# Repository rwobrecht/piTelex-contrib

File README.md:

# Willkommen zu meinem piTelex-contrib

Hier sammle ich Anpassungen und anderes, was ich rund um piTelex mal entwickelt habe, in der Hoffnung, dass der eine oder andere piTelex-Nutzer mit der einen oder anderen Sache etwas anfangen kann, und -nicht zu vergessen- damit ich die Sachen bei Bedarf auch selbst wiederfinde :-)

## piTelex-Hardware für TW39

- ### Kombi-Platine für Linienstrommaschinen mit und ohne Fernschaltgerät

  jumper-konfigurierbar für Betrieb mit/ohne FSG

  - [TW39-Platine](TW39/Kombiversion/TW39-mit-Powersave) für einen RaspBerry Pi mit Powersave-Funktion sowohl für die 230V-Versorgung als auch für die Linienstromversorgung.
  - [TW39-Stromversorgung](TW39/Kombiversion/Stromversorgung-für-TW39-mit-Powersave) dazu passend, mit Powersave-Unterstützung.

- ### als Fernschaltgerät-Ersatz für Linienstrommaschinen mit 24V-LED-Treiber

  * [TW39-Platine](TW39/Ohne-FSG/TW39-ohne-FSG-mit-Powersave) für einen RaspBerry Pi als vollwertiger FSG-Ersatz mit Powersave-Funktion sowohl für die 230V-Versorgung als auch für die Linienstromversorgung

  * [TW39-Stromversorgung](TW39/Ohne-FSG//Stromversorgung-für-TW39-ohne-FSG-mit-Powersave) mit reduzierter Linienspannung, dazu passend. 

  * [Aufbaubeispiel mit Steckernetzteil und Kleinspannung](TW39/Ohne-FSG/Aufbaubeispiel/)

- ### [Adapterplatinchen zum Anschluss eines Tastwahlblocks](TW39/TWB/)

- ###  für V.10
  * [V.10-Platine](V10/V.10-3-mit-Powersave) für die Anbindung von TeKaDe FS200/FS220 mit Powersave-Funktion

  * [V.10-Stromversorgung](V10/V.10-3-Stromversorgung-mit-Powersave) dazu passend, mit Powersave-Unterstützung für die 230V-Versorgung.

  * [Aufbaubeispiel](V10/Aufbaubeispiel/README.md)

**Fragen oder Anregungen gerne an `telex(at)freenet.de`.**

**Da bei meinem PCB Hersteller immer eine Mindestabnahme gilt, und ich selber die Platinen nicht alle "verbrauchen" kann, gebe ich vorhandenes Material gerne weiter. Bei Interesse einfach nachfragen!**

## Software: RPi-Image mit piTelex

- ### RPi-Image mit piTelex

  Zu den o.a. Hardware-Varianten  [passendes Software-Image](./soft/rpi-image/README.md) für RaspBerry Pi's. Es enthält ein fertig vorinstalliertes und lauffähiges piTelex.
  
- ### Device modul für LCD1602 Display

  Statt der LEDs (oder ergänzend) ein [zweizeiliges LCD](./soft/LCD1602/README.md)  **mit Rufnummernanzeige** einbinden

## HOWTOS und so...

Unter [HOWTO](HOWTO) ...passenderweise :-)

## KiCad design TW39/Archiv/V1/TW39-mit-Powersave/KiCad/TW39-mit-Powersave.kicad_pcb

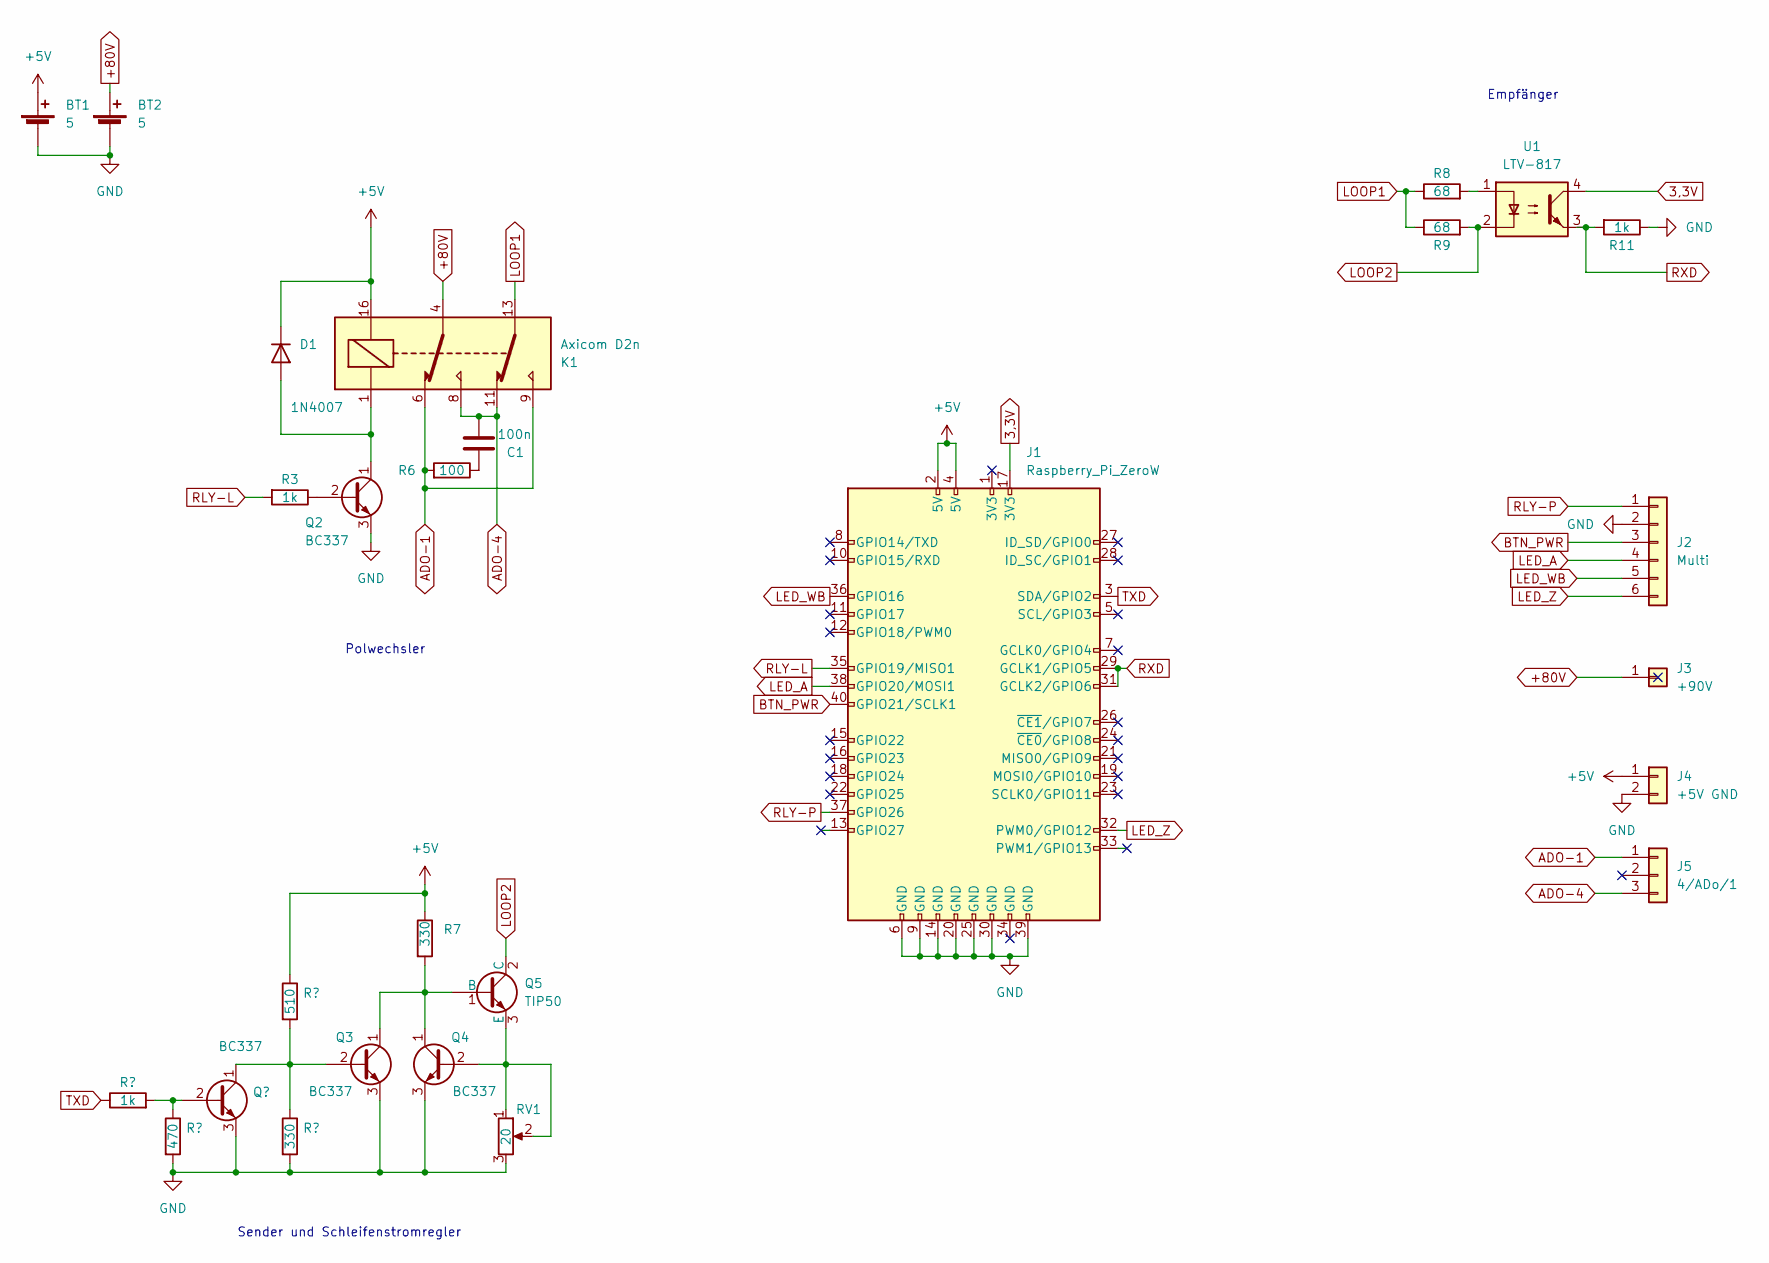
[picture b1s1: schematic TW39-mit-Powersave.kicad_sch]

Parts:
BT1, BT2: 5
C1: 100n; C_Rect_L11.0mm_W5.1mm_P10.00mm_MKT
D1: 1N4007; D_DO-41_SOD81_P7.62mm_Horizontal
J1: Raspberry_Pi_ZeroW; PinSocket_2x20_P2.54mm_Horizontal
J2: Multi; Molex_KK-254_AE-6410-06A_1x06_P2.54mm_Vertical
J3: +90V; PinHeader_1x01_P2.54mm_Vertical
J4: +5V GND; Molex_KK-254_AE-6410-02A_1x02_P2.54mm_Vertical
J5: 4/ADo/1; Molex_KK-254_AE-6410-03A_1x03_P2.54mm_Vertical
K1: Axicom D2n; Relay_DPDT_Omron_G5V-2
Q1, Q2, Q3, Q4: BC337; TO-92_Inline_Wide
Q5: TIP50; Molex_KK-254_AE-6410-04A_1x04_P2.54mm_Vertical
R1, R3, R11: 1k; R_Axial_DIN0207_L6.3mm_D2.5mm_P2.54mm_Vertical
R2: 470; R_Axial_DIN0207_L6.3mm_D2.5mm_P2.54mm_Vertical
R4: 510; R_Axial_DIN0207_L6.3mm_D2.5mm_P2.54mm_Vertical
R5, R7: 330; R_Axial_DIN0207_L6.3mm_D2.5mm_P2.54mm_Vertical
R6: 100; R_Axial_DIN0207_L6.3mm_D2.5mm_P10.16mm_Horizontal
R8, R9: 68; R_Axial_DIN0207_L6.3mm_D2.5mm_P2.54mm_Vertical
RV1: 20; Potentiometer_Bourns_3296W_Vertical
U1: LTV-817; DIP-4_W7.62mm

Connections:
3,3V: J1.17 (3V3), U1.4
+5V: BT1.1 (+), D1.1 (K), J1.2 (5V), J1.4 (5V), J4.1, K1.16, R4.1, R7.1
+80V: BT2.1 (+), J3.1, K1.4
ADO-1: J5.1, K1.6, K1.9, R6.2
ADO-4: C1.2, J5.3, K1.8, K1.11
BTN_PWR: J1.40 (GPIO21/SCLK1), J2.3
GND: BT1.2 (-), BT2.2 (-), J1.6 (GND), J1.9 (GND), J1.14 (GND), J1.20 (GND), J1.25 (GND), J1.30 (GND), J1.39 (GND), J2.2, J4.2, Q1.3 (E), Q2.3 (E), Q3.3 (E), Q4.3 (E), R2.2, R5.2, R11.1, RV1.3
LED_A: J1.38 (GPIO20/MOSI1), J2.4
LED_WB: J1.36 (GPIO16), J2.5
LED_Z: J1.32 (PWM0/GPIO12), J2.6
LOOP1: K1.13, R8.1, R9.1
LOOP2: Q5.2 (C), R9.2, U1.2
unnamed: C1.1, R6.1
unnamed: D1.2 (A), K1.1, Q2.1 (C)
unnamed: Q1.2 (B), R1.2, R2.1
unnamed: Q1.1 (C), Q3.2 (B), R4.2, R5.1
unnamed: Q2.2 (B), R3.1
unnamed: Q3.1 (C), Q4.1 (C), Q5.1 (B), R7.2
unnamed: Q4.2 (B), Q5.3 (E), RV1.1, RV1.2
unnamed: R8.2, U1.1
RLY-L: J1.35 (GPIO19/MISO1), R3.2
RLY-P: J1.37 (GPIO26), J2.1
RXD: J1.29 (GCLK1/GPIO5), J1.31 (GCLK2/GPIO6), R11.2, U1.3
TXD: J1.3 (SDA/GPIO2), R1.1

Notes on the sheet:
Polwechsler
Sender und Schleifenstromregler
Empfänger

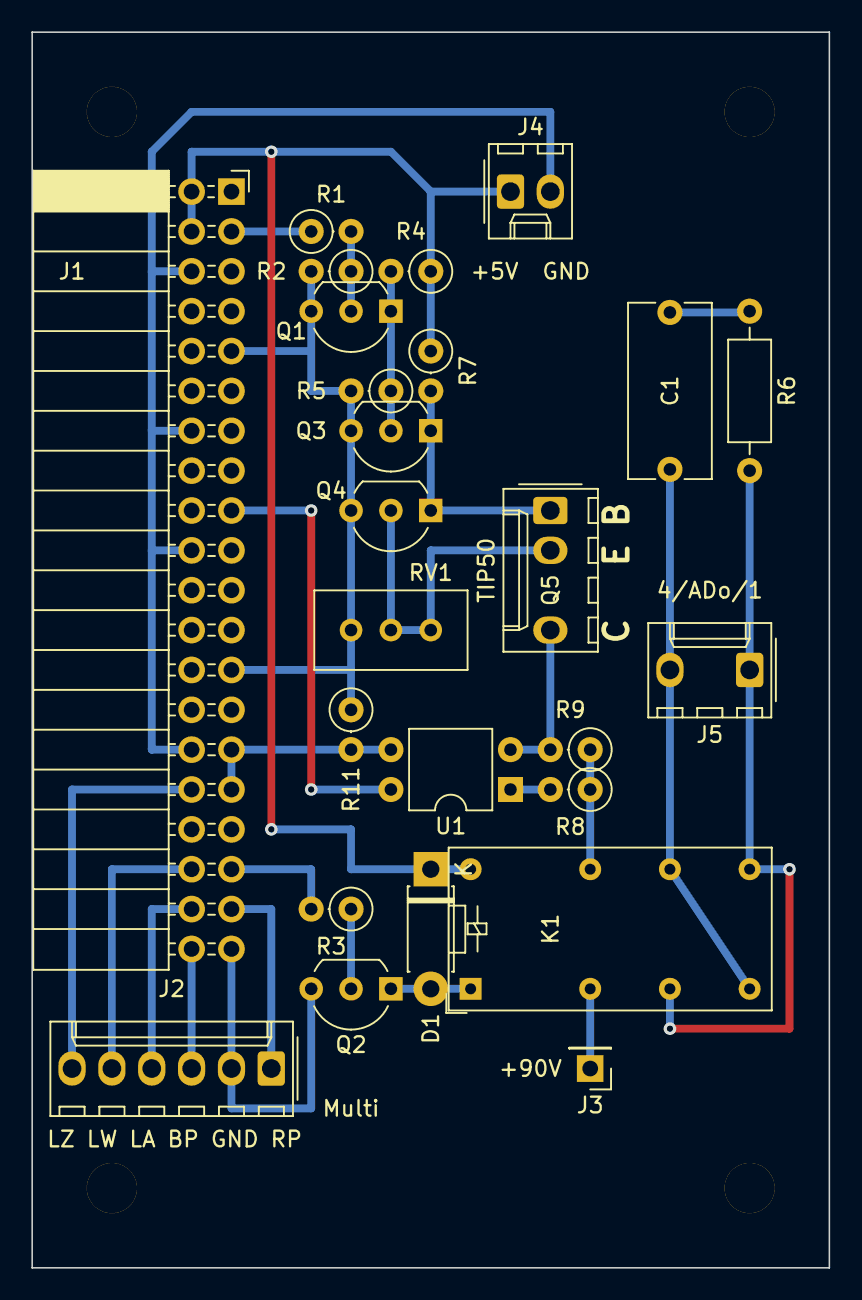
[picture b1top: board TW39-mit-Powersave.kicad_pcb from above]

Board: 2 copper layers, 50.8 x 78.7 mm, 25 parts (0 on the bottom side), 24 nets.

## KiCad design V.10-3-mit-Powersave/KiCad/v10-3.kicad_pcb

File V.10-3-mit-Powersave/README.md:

# Platine für piTelex V.10 (FS200/220)

## Die Funktionsmerkmale
Die hier beschriebene Platine eignet sich zum Anschluss eines Fernschreibers mit V.10 Schnittstelle (TeKaDe FS200/FS220) ***ohne*** Fernschaltgerät (FAG200 o.ä.). 

Die nötige Stromversorgung (+5V= ) muss extern bereitgestellt werden. Ein passender Bauvorschlag, der auch die Powersave-Funktion unterstützt, findet sich im [entsprechenden Unterverzeichnis](https://github.com/rwobrecht/piTelex-contrib/blob/main/V.10-3-Powersupply) des repositories.

Die Platine/Schaltung verwendet drei LEDs:
* LED_Z blinkt bei Standby der Software ("ZZ"-Zustand) und leuchtet kontinuierlich bei Betriebsbereitschaft ("Z"-Zustand). Der Blinkrhythmus kann in `telex.json` mit `LED_Z_heartbeat` eingestellt werden (s.u.).
* LED_WB leuchtet bei Wählbereitschaft
* LED_A leuchtet bei bestehender i-telex-Verbindung

Es ist möglich, eine Stromsparschaltung zu aktivieren. Dazu kann die Stromversorgung aus dem [Bauvorschlag](https://github.com/rwobrecht/piTelex-contrib/blob/main/V10-3-Powersupply) verwendet werden. Der Pin 3 des Steckers J3 dieser Platine steuert das Leistungsrelais auf der Stromversorgungsplatine, an deren Kontaktblock die Steckdose zur Versorgung des Fernschreibers angeklemmt wird. Außerdem muss in der telex.json die Stromsparschaltung aktiviert werden. Der `telex.json`-Ausschnitt weiter unten enthält alle hierfür nötigen Einstellungen. Ist die Stromsparschaltung aktiv, dann gilt:

* Bei ankommendem Anruf schaltet piTelex die Stromversorgung ein und nach Verbindungsende automatisch auch wieder aus.
* Für einen ausgehenden Anruf drückt man kurz die am `pin_button_PT` angeschlossene Taste, um das Stromrelais einzuschalten. Nach Verbindungsende wird der FS durch erneutes Drücken der Taste oder automatisch nach einer vorwählbaren Zeit (`power_button_timeout`) wieder ausgeschaltet.

---

## Die Schaltung

Für die Ansteuerung des Fernschreibers werden nur die Signale TXD, RXD und CTS benötigt. Damit die gesendeten Zeichen in rot, die empfangenen in schwarz gedruckt werden, ist mittels eines 74HCT00 Bausteins ein hardware-loopback realisiert. Die 74**HCT**xx-Serie ist für die 3,3V-Logik angepasst, andere Familien (LS,...) müssen nicht zwingend funktionieren. Die V.10-Schnittstelle ist sehr ähnlich zur V.24 bzw. RS232-Schnittstelle und arbeitet mit symmetrischen Spannungen. Daher kann zur Pegelumwandlung von TTL-Signalen ein MAX232 verwendet werden.
Um den TTL-Ausgangspegel des MAX232 auf 3,3V für den RPi herabzusetzen, werden zwei Spannungsteiler R7/R5 und R8/R6 eingesetzt.

Die Schaltung verwendet **nicht** die Standard-GPIO-Belegung!  Siehe unten.

---
## Die Platine

Die Platine ist zweilagig mit KiCad entwickelt worden, die Projektdaten liegen im Unterverzeichnis [KiCad](KiCad).

Als SBC ist ein Raspberry Pi Zero WH vorgesehen, der einfach seitlich auf die zweireihige Kontaktleiste gesteckt wird. Es passen natürlich auch andere RPi mit 40-poligem GPIO-Sockel.
Für die Steuerung eines einzelnen V.10-Fernschreibers ist ein  RPi Zero jedenfalls mehr als ausreichend.

### Bauteileliste

| Bauteil     | Wert      |
| ----------- | --------- |
| C1,C3       | 3,3µF/16V |
| C2,C4,C5,C6 | 1µF/16V   |
| R3,R4,R9    | 470 Ohm   |
| R5,R6       | 4K7       |
| R1,R2,R7,R8 | 2k2       |
| U1          | 74HCT00   |
| U2          | MAX232    |

Alle Widerstände 0,125 W oder 0,25W

### Anschlüsse

Die Platine bietet folgende Anschlussmöglichkeiten:

|Stecker|Pin|Name|Ein-/Ausgang|Beschreibung|
|-------|---|----|------------|---------------------------|
|J1     |1  |GND |            ||
|J1     |2  |TXD |A           | optional: LED zur Anzeige von TXD (Anode, LED ohne Vorwiderstand gegen J1/Pin1 anschließen) |
|J1     |3  |RXD |A           | optional: LED zur Anzeige von RXD (Anode, LED ohne Vorwiderstand gegen J1/Pin1 anschließen) |
|---|||||
|J2     |*  |    |            | RaspBerryPi GPIO|
|---|||||
|J3     |1  |GND |A           ||
|J3     |2  |D1  |E           |verbinde auf Pin 2 der DSUB25 Buchse|
|J3     |3  |D2  |A           |verbinde auf Pin 3 der DSUB25 Buchse|
|J3     |4  |S2  |E           |verbinde auf Pin 4 der DSUB25 Buchse|
|---|||||
|J4     |1  |+5V |E           |+5V Versorgungsspannung    |
|J4     |2  |GND |E           | Massepotential für +5V |
|J4     |3  |RLY |A           | Steuerspannung Relais|
|---|||||
|J5     |1  |    |A           |Taster Powersave|
|J5     |2  |    |E           |Taster Powersave|
|---|||||
|J6     |1  |GND| Rückleiter ||
|J6     |2  | LED_Z|A        | Anode LED_Z ohne Vorwiderstand anschließen gegen J6/Pin1|
|J6     |3  | LED_WB|A       | Anode LED_WB ohne Vorwiderstand anschließen gegen J6/Pin1|
|J6     |2  | LED_A|A        | Anode LED_A ohne Vorwiderstand anschließen gegen J6/Pin1|

---

## Die DB25-Buchse zum FS200
Die Buchse braucht folgende Pinbelegung:

|Pin|Signal|von Stecker/Pin|
|-|-|-|
|2|D1|J3/2|
|3|D2|J3/3|
|4|S2|J3/4|
|7,9,11-14|GND|J3/1|

---

## Die `telex.json`

Die Schaltung verwendet **nicht** die Standard-GPIOs von piTelex, daher füge ich einen passenden Ausschnitt aus der `telex.json` Datei mit den korrekten GPIO-Nummern bei:

```JSON

    "RPiTTY_FS200": {
      "type": "RPiTTY",
      "enable": true,
      "mode": "V10",
      "pin_txd": 11,
      "pin_rxd": 9,
      "use_observe_line": true,
      "pin_observe_line": 10,
      "inv_observe_line": true,
      "nZZ_observe_line": true,
      "baudrate": 200,
      "coding": 0,
      "loopback": false
    },
    "RPiCtrl": {
      "type": "RPiCtrl",
      "enable": true,
      "pin_number_switch": 0,
      "pin_button_PT": 26,
      "pin_LED_A": 19,
      "pin_LED_WB": 13,
      "pin_LED_WB_A": 0,
      "pin_LED_Z": 6,
      "pin_power": 4,
      "inv_power": false
    },
    
(....)  
  
  },
  "wru_id": "123456 dummy d",
  "wru_replace_always": false,
  "continue_with_no_printer": false,
  "power_off_delay": 3,          # 3s nach Ende der Verbindung schaltet die Maschine ab
  "power_button_timeout": 7200,  # nach 2h Betrieb schaltet die Maschine immer ab
  "dial_timeout": "+"            # plus-dialing wie im EDS (nach Eingabe der Ziffern muss  "+" eingegeben werden zum Starten der Wahl )
}

```
---

## Abschließend der unvermeidliche Disclaimer:
Auch wenn dieser Schaltungsvorschlag in mehreren Exemplaren unproblematisch funktioniert: für korrekte Funktion und für mögliche Schäden, verursacht durch Verwendung der in diesem Repository bereitgestellten Informationen, kann ich keine Haftung übernehmen. 

Für die Einhaltung der sicherheitstechnischen Vorschriften und anerkannten Regeln der Technik, insbesondere im Bereich der elektrischen Sicherheit, ist jeder Anwender selbst verantwortlich.

Unabhängig davon würde ich mich über Rückmeldungen zu Doku-Fehlern, Funktion oder möglichen Verbesserungen sehr freuen.

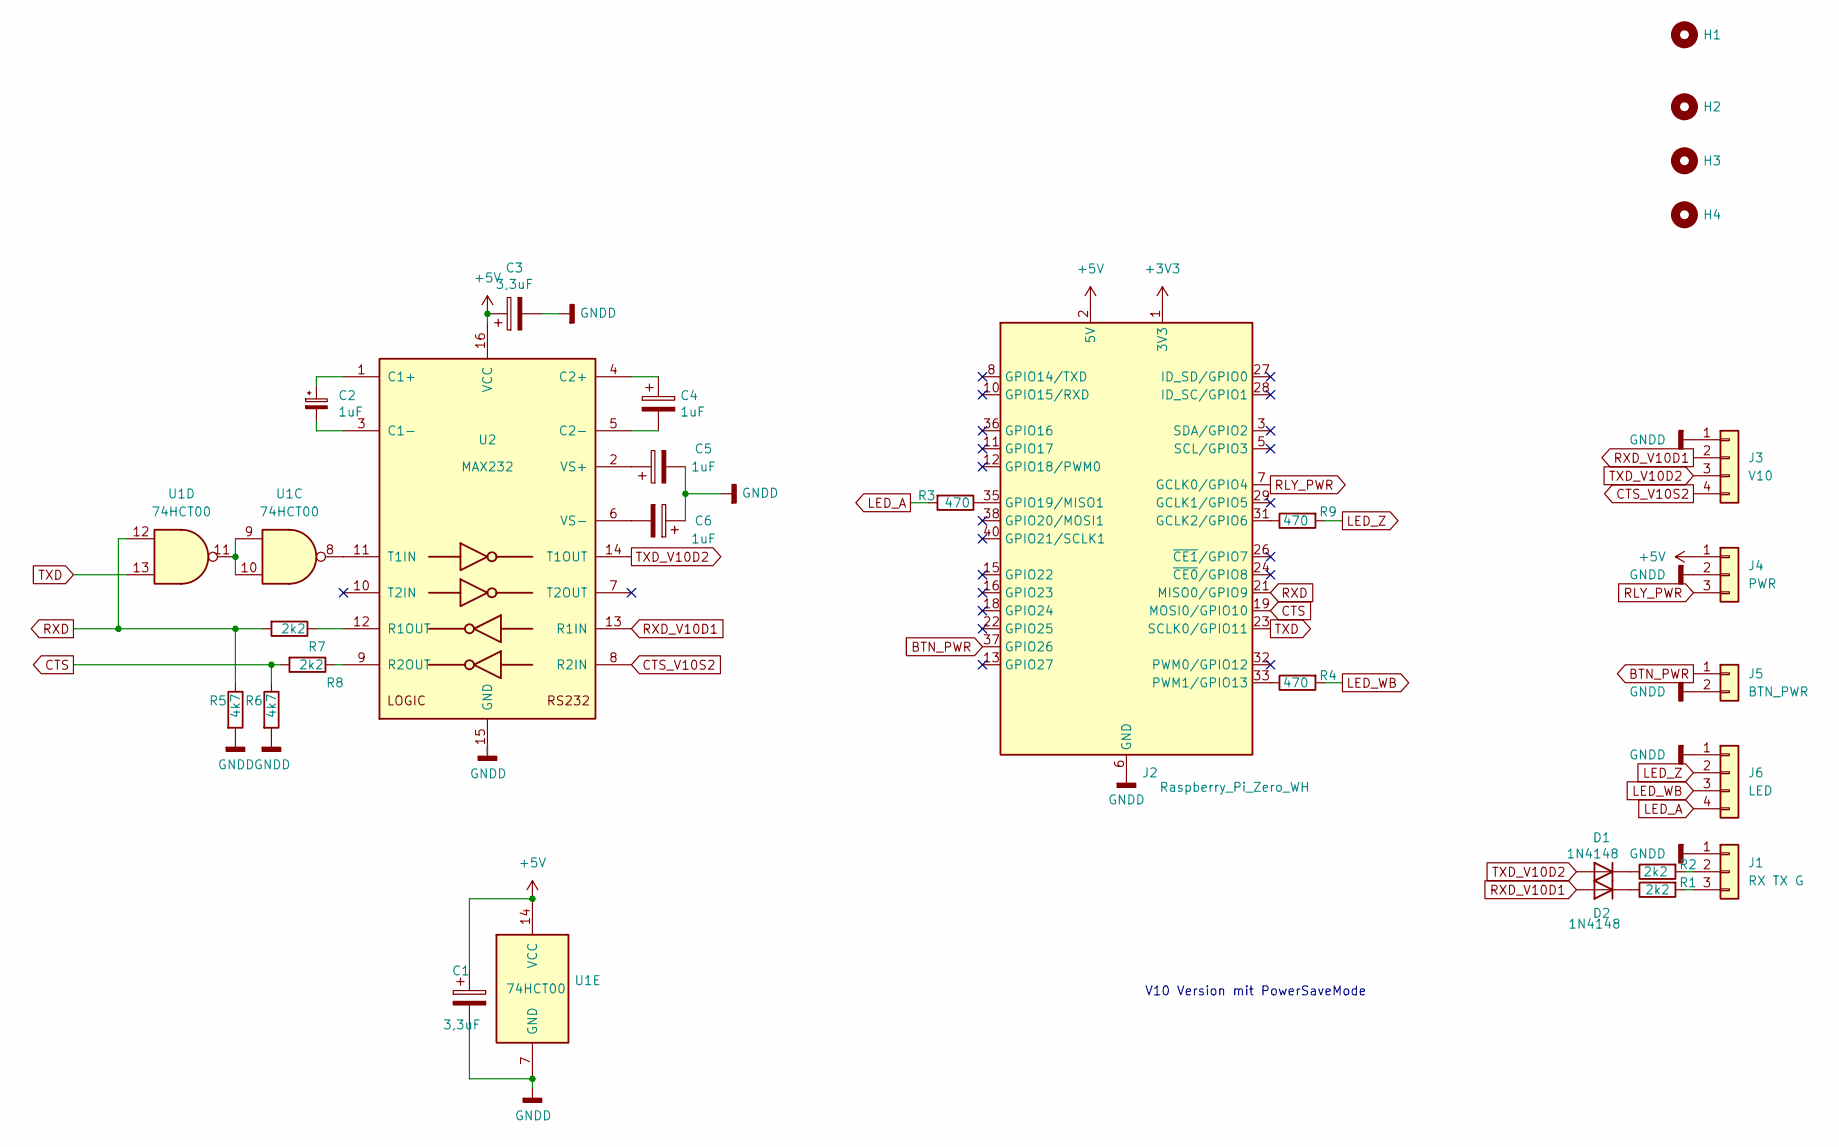
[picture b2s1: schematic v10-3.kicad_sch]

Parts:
C1, C3: 3,3uF; CP_Radial_Tantal_D4.5mm_P2.50mm
C2, C4, C5, C6: 1uF; CP_Radial_Tantal_D4.5mm_P2.50mm
D1, D2: 1N4148; D_DO-15_P2.54mm_Vertical_AnodeUp
H1, H2, H3, H4: MountingHole; MountingHole_3.2mm_M3
J1: RX TX G; Molex_KK-254_AE-6410-03A_1x03_P2.54mm_Vertical
J2: Raspberry_Pi_Zero_WH; PinSocket_2x20_P2.54mm_Horizontal
J3: V10; Molex_KK-254_AE-6410-04A_1x04_P2.54mm_Vertical
J4: PWR; Molex_KK-254_AE-6410-03A_1x03_P2.54mm_Vertical
J5: BTN_PWR; Molex_KK-254_AE-6410-02A_1x02_P2.54mm_Vertical
J6: LED; Molex_KK-254_AE-6410-04A_1x04_P2.54mm_Vertical
R1, R2: 2k2; R_Axial_DIN0309_L9.0mm_D3.2mm_P2.54mm_Vertical
R3, R4, R9: 470; R_Axial_DIN0309_L9.0mm_D3.2mm_P2.54mm_Vertical
R5, R6: 4k7; R_Axial_DIN0207_L6.3mm_D2.5mm_P2.54mm_Vertical
R7, R8: 2k2; R_Axial_DIN0207_L6.3mm_D2.5mm_P2.54mm_Vertical
U1: 74HCT00; DIP-14_W7.62mm
U2: MAX232; DIP-16_W7.62mm

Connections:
+3V3: J2.1 (3V3), J2.17 (3V3)
+5V: C1.1, C3.1, J2.2 (5V), J2.4 (5V), J4.1, U1.14 (VCC), U2.16 (VCC)
BTN_PWR: J2.37 (GPIO26), J5.1
CTS: J2.19 (MOSI0/GPIO10), R6.1, R8.2
CTS_V10S2: J3.4, U2.8 (R2IN)
GNDD: C1.2, C3.2, C5.2, C6.1, J1.1, J2.6 (GND), J2.9 (GND), J2.14 (GND), J2.20 (GND), J2.25 (GND), J2.30 (GND), J2.34 (GND), J2.39 (GND), J3.1, J4.2, J5.2, J6.1, R5.2, R6.2, U1.7 (GND), U2.15 (GND)
LED_A: J6.4, R3.2
LED_WB: J6.3, R4.2
LED_Z: J6.2, R9.2
unnamed: D1.1 (K), R2.1
unnamed: D2.1 (K), R1.1
unnamed: J1.2, R2.2
unnamed: J1.3, R1.2
unnamed: J2.31 (GCLK2/GPIO6), R9.1
unnamed: J2.35 (GPIO19/MISO1), R3.1
unnamed: J2.33 (PWM1/GPIO13), R4.1
unnamed: U1.9, U1.10, U1.11
unnamed: C2.1, U2.1 (C1+)
unnamed: C2.2, U2.3 (C1-)
unnamed: C4.1, U2.4 (C2+)
unnamed: C4.2, U2.5 (C2-)
unnamed: R7.1, U2.12 (R1OUT)
unnamed: R8.1, U2.9 (R2OUT)
unnamed: U1.8, U2.11 (T1IN)
unnamed: C5.1, U2.2 (VS+)
unnamed: C6.2, U2.6 (VS-)
RLY_PWR: J2.7 (GCLK0/GPIO4), J4.3
RXD: J2.21 (MISO0/GPIO9), R5.1, R7.2, U1.12
RXD_V10D1: D2.2 (A), J3.2, U2.13 (R1IN)
TXD: J2.23 (SCLK0/GPIO11), U1.13
TXD_V10D2: D1.2 (A), J3.3, U2.14 (T1OUT)

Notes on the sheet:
V10 Version mit PowerSaveMode

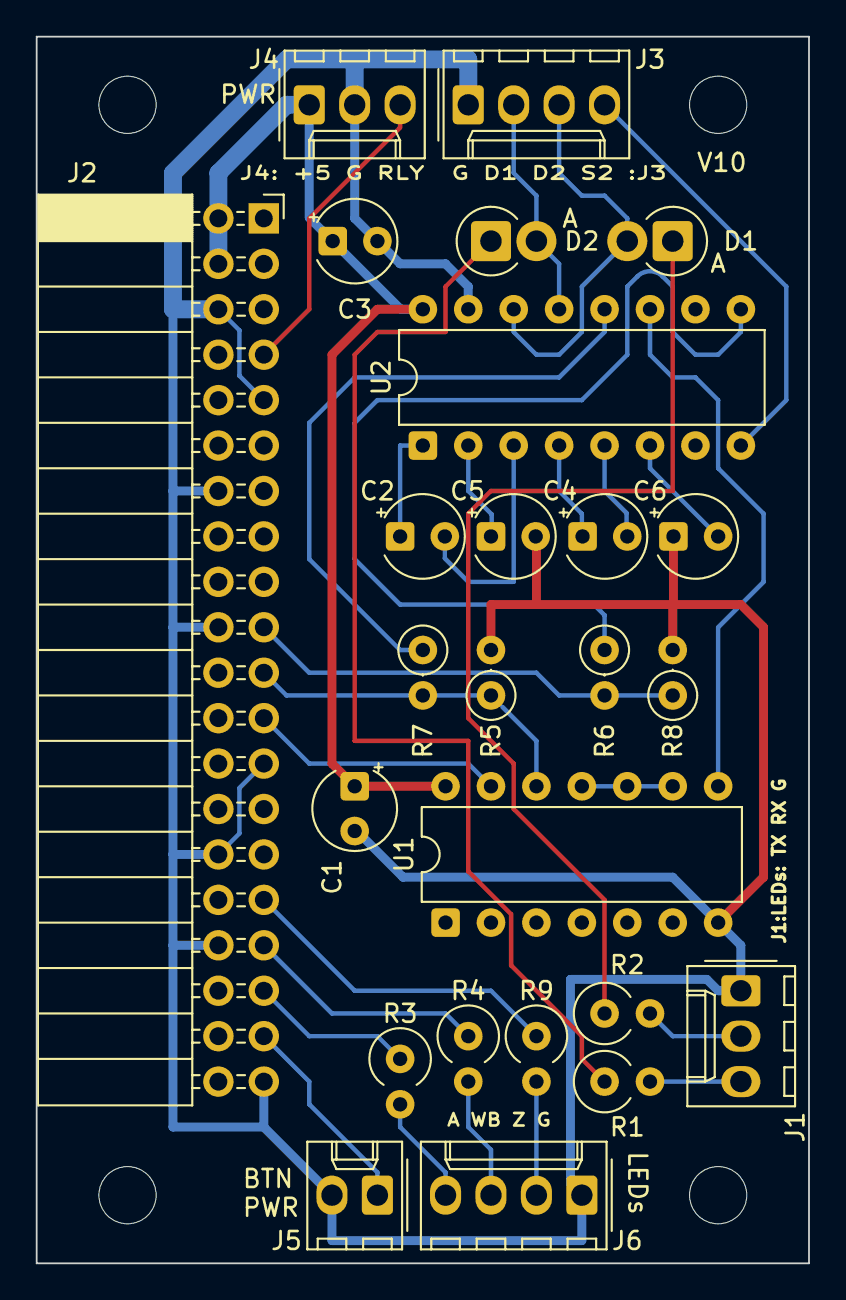
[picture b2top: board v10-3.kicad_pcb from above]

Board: 2 copper layers, 43.2 x 68.6 mm, 29 parts (0 on the bottom side), 30 nets.

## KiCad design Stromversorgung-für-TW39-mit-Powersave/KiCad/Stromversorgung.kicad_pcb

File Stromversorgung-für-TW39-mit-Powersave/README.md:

## Platine für piTelex TW39 (Stromversorgung)

## Die Funktion
Die hier beschriebene Platine liefert zum einen eine galvanisch vom Netz getrennte Linienstromversorgung mit ca 90V Leerlaufspannung und etwa 75V bei 40mA Last. Zum anderen stellt sie +5V bei max 2A für die Versorgung eines RPi Zero WH und die übrige Steuerelektronik bereit. Dafür ist ein fertiger Netzteilbaustein Meanwell IRM 10-5 verwendet. Dieser Baustein ist in Schutzklasse II ausgeführt und u.a. TÜV-zertifiziert:

Darüber hinaus gibt es einen relaisgeschalteten 230V-Ausgang zum Anschluss des Fernschreibers/des Fernschaltgeräts. Wird der Steuereingang "RP" mit dem entsprechenden Ausgang auf der TW39-Platine verbunden, kann damit eine Stromsparschaltung realisiert werden, so dass das Fernschreibequipment nur Netzspannung erhält für die Dauer eines ankommenden Fernschreibens und bei manueller Betätigung des Tasters "PT" ([siehe TW39-Platine](https://github.com/rwobrecht/piTelex-contrib/tree/main/TW39-mit-Powersave) ).

## Die Platine

Das Platinenlayout ist auf Einfachheit hin getrimmt. Man kann sie zweilagig herstellen, aber auch als einlagig kupferkaschierte Platine ausführen, dann muss lediglich eine Drahtbrücke eingesetzt werden, die ansonsten durch die zweite Kupferlage realisiert wird. Die Leitungsführung ist in Standradrastermaß von 1/10 Zoll gehalten, so dass das Layout unverändert auch auf einer handelsüblichen Punktrasterplatine ganz "zu Fuß" umgesetzt werden kann.

Besonderes Augenmerk habe ich auf ausreichende Leiterbahnabstände im Hochspannnungsbereich gelegt. 
Wenn man die Schaltung auf einer Punktrasterplatine aufbaut, müssen die nicht verwendeten Lötstützpunkte im Bereich der Netzspannung und der Linienstromversorgung weggefräst werden, denn die 0,4mm "Luft" 
zwischen zwei Lötstützpunkten sind bei diesen Spanungen sicher nicht ausreichend. 

## Die Stückliste

|Bez.|Bauteil|Bemerkung|
|----|-------|---------|
| J1,J4| Schraubklemme 2pol  RM 10,16|
| J3|PinHeader 2pol RM2,54mm|
| J2,J5|PinHeader 1pol|
|T1| Trafo 230V / 2x24V 100mA |z.B. GERTH 421.48.2| 
|D1| 1N4007|
|D2|BrGleichrichter DF08M| o.ä.|
|F1|Sicherungshalter 5x20mm|
|K1|Relais DPDT 250V/8A, 5V Spule | z.B. FINDER-40.52|
|R1|1k 0,125W|
|R2|180k 0,25W|
|C1| 330 µF 200V|
|U1|BC337|
|PS1| MeanWell IRM 10-5|

## Die Sicherheit
Es ist eine **drei**adrige Netzzuleitung **mit Schutzleiter (PE)** zu verwenden, der auf die Ausgangs-Schukosteckdose für den Fernschreiber durchzuverbinden ist.
Die Eingangsseite (230V) sollte mit 1A träge abgesichert werden. Das ist ausreichend für den Betrieb eines Fernschreibers und des Vorschaltgeräts. Diese Sicherung ist nicht auf der Platine vorgesehen, sondern wird bei mir über eine im Gehäuse verbaute Kaltgeräte-Einbaubuchse mit integriertem Sicherungshalter realisiert. Außerdem empfiehlt es sich, vor diese Netzteilschaltung ein Fehlerstromschutzorgan mit max 30mA Abschaltstrom (Personenschutzschalter) einzusetzen (sofern nicht bauseitig bereits vorhanden), um Schäden duch mögliche Isolationsprobleme insbesondere bei älteren Maschinen abfangen zu können. 

Der Trafo ist sekundärseitig mit 100mAT abzusichern. Da der Linienstrom auf der TW39-Platine **geregelt** wird (auch bei Kurzschluss des Linienstromkreises), ist ein Ansprechen der Feinsicherung in der Praxis so gut wie ausgeschlossen, deshalb ist sie ohne Komforteinbuße auf der Platine im Geräteinneren verbaut.

Das Ganze wird sinnvollerweise in ein Vollkunststoffgehäuse Schutzklasse II eingebaut. Von außen berührbare Metallteile (bspw. Metallfrontplatte o.ä) mit ausreichendem Leiterquerschnitt schutzerden!

## Abschließend der unvermeidliche Disclaimer:
Auch wenn dieser Schaltungsvorschlag in mehreren Exemplaren seit Jahren unproblematisch funktioniert: für korrekte Funktion und für mögliche Schäden, verursacht durch Verwendung der in diesem Repository bereitgestellten Informationen, kann ich keine Haftung übernehmen. 

Für die Einhaltung der sicherheitstechnischen Vorschriften und anerkannten Regeln der Technik, insbesondere im Bereich der elektrischen Sicherheit, ist jeder Anwender selbst verantwortlich.

Unabhängig davon würde ich mich über Rückmeldungen zu Funktion oder möglichen Verbesserungen sehr freuen.

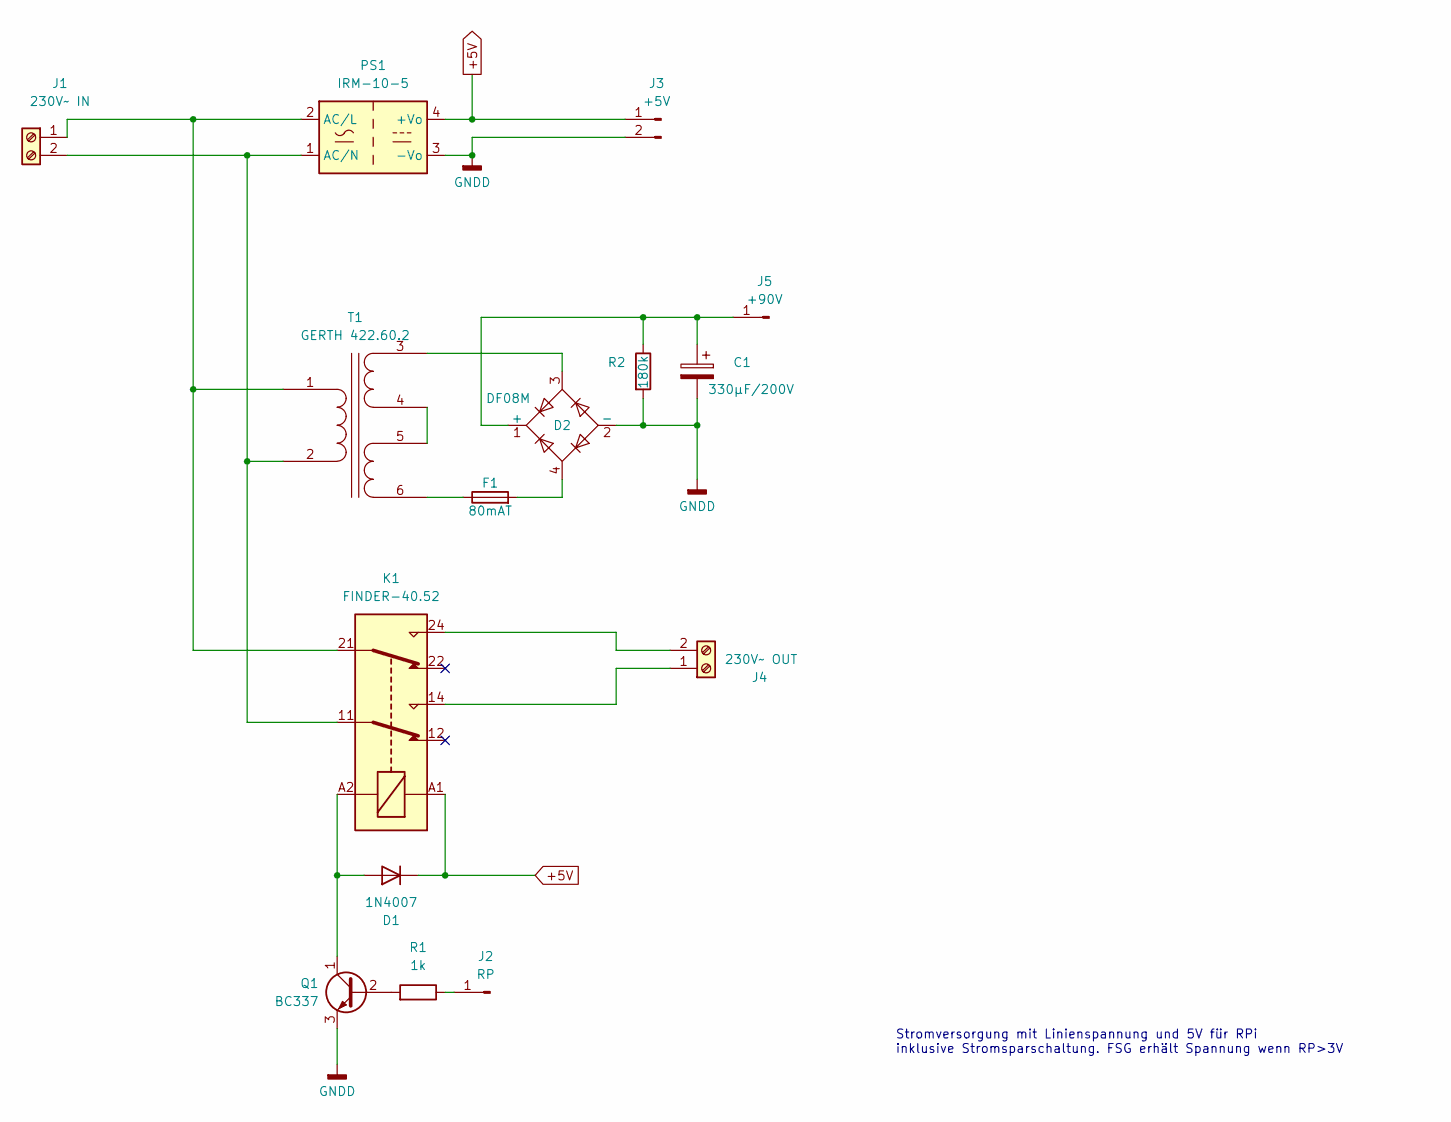
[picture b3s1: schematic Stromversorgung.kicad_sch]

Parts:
C1: 330µF/200V; CP_Radial_D22.0mm_P10.00mm_SnapIn
D1: 1N4007; D_DO-41_SOD81_P7.62mm_Horizontal
D2: DF08M; Diode_Bridge_DIP-4_W7.62mm_P5.08mm
F1: 80mAT; Fuseholder_Clip-5x20mm_Eaton_1A5601-01_Inline_P20.80x6.76mm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
J1: 230V~ IN; TerminalBlock_RND_205-00067_1x02_P7.50mm_Horizontal
J2: RP; PinHeader_1x01_P2.54mm_Vertical
J3: +5V; Molex_KK-254_AE-6410-02A_1x02_P2.54mm_Vertical
J4: 230V~ OUT; TerminalBlock_RND_205-00067_1x02_P7.50mm_Horizontal
J5: +90V; PinHeader_1x01_P2.54mm_Vertical
K1: FINDER-40.52; Relay_DPDT_Finder_40.52
PS1: IRM-10-5; Converter_ACDC_MeanWell_IRM-10-xx_THT
Q1: BC337; TO-92_Inline_Wide
R1: 1k; R_Axial_DIN0207_L6.3mm_D2.5mm_P10.16mm_Horizontal
R2: 180k; R_Axial_DIN0207_L6.3mm_D2.5mm_P10.16mm_Horizontal
T1: GERTH 422.60.2; Transformer_CHK_EI42-5VA_2xSec_6pin

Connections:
+5V: D1.1 (K), J3.1, K1.A1, PS1.4 (+Vo)
GNDD: C1.2, D2.2 (-), J3.2, PS1.3 (-Vo), Q1.3 (E), R2.2
unnamed: D1.2 (A), K1.A2, Q1.1 (C)
unnamed: C1.1, D2.1 (+), J5.1, R2.1
unnamed: D2.4, F1.2
unnamed: J1.1, K1.21, PS1.2 (AC/L), T1.1 (AA)
unnamed: J1.2, K1.11, PS1.1 (AC/N), T1.2 (AB)
unnamed: J2.1, R1.1
unnamed: J4.1, K1.14
unnamed: J4.2, K1.24
unnamed: Q1.2 (B), R1.2
unnamed: D2.3, T1.3 (SA)
unnamed: T1.4 (SB), T1.5 (SC)
unnamed: F1.1, T1.6 (SD)

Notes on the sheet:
Stromversorgung mit Linienspannung und 5V für RPi inklusive Stromsparschaltung. FSG erhält Spannung wenn RP>3V

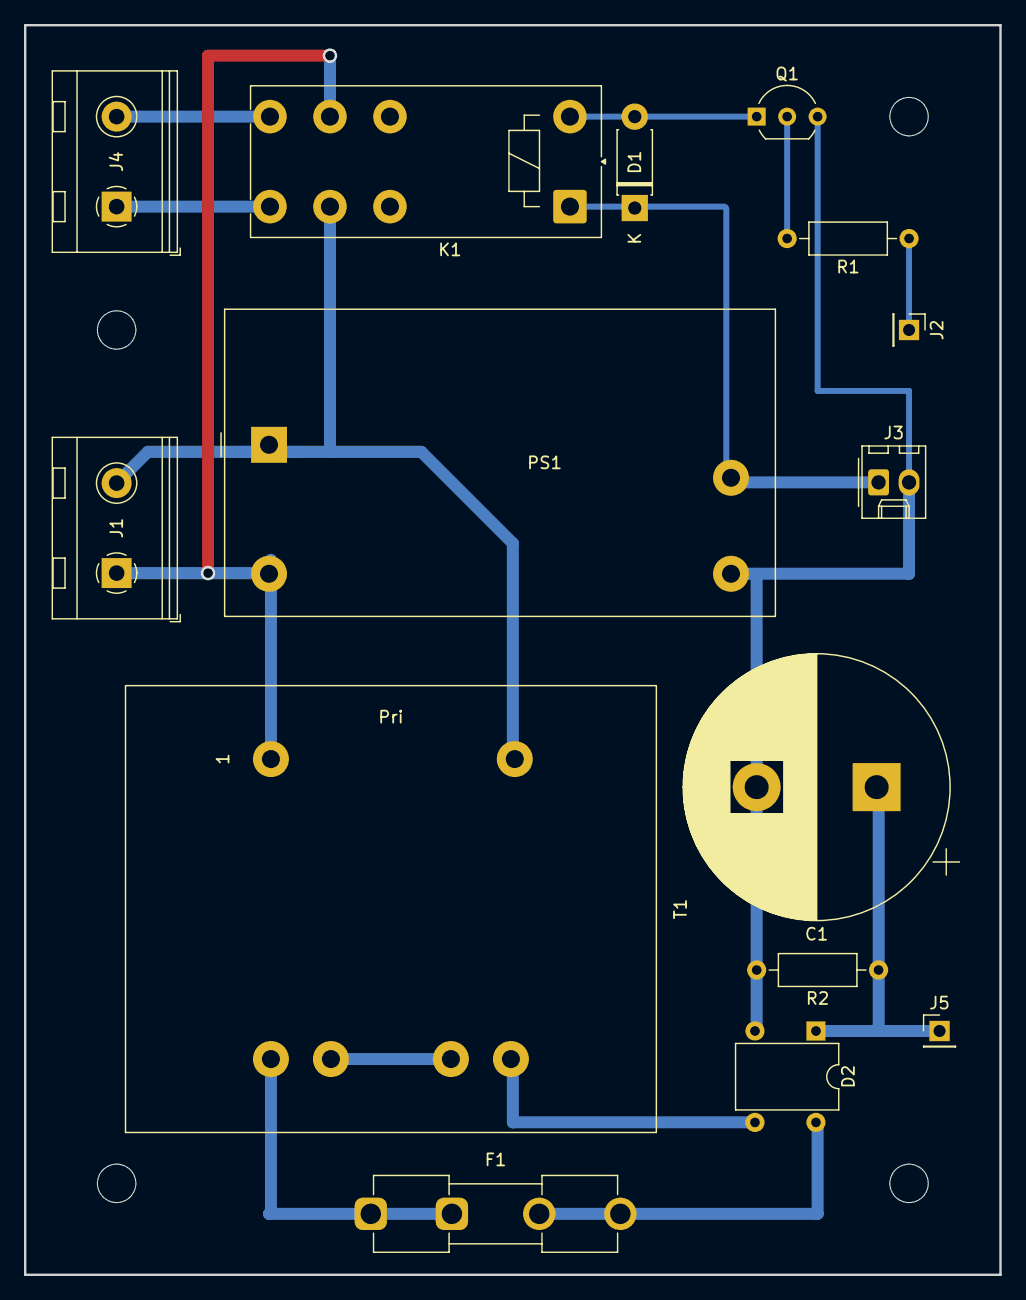
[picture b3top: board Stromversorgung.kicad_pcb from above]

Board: 2 copper layers, 81.3 x 104.1 mm, 15 parts (0 on the bottom side), 14 nets.

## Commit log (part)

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2025-01-17 Initial upload
2025-01-21 Netzteil upload
2025-01-23 Aufbaufotos
2025-03-07 Update README.md
    typo...
2025-03-07 bugfix in KiCad
2025-06-26 Update README.md
    pin_relay=19!
2025-08-22 relaunch, added V10-3
2025-08-22 Aktualisieren von README.md
2025-09-24 Layout-Update für V10
2025-09-24 TW39V2 hinzugefügt
2025-10-12 Ohne-FSG hinzugefügt, READMEs angepasst
2025-10-17 Fix GPIO configuration in README.md
    Updated the GPIO configuration section in the README.
2025-10-19 image added
2025-10-21 Update README with power-saving circuit details
2025-10-21 Fix link to TW39 circuit diagram in README
    Updated link to the TW39 circuit diagram in the README.
2025-10-21 Fix link for V.10 power supply in README
2025-10-25 Refactor README.md for improved structure
    Updated formatting and headings in README for clarity.
2025-10-25 Update README with clearer image writing instructions
    Rephrase instructions for writing the image to the µSD card and remove the dd command.
2025-10-25 Clarify storage and add disclaimer in README
    Updated README to clarify storage requirements and added a disclaimer about the image functionality.
2025-10-30 Update README with locale and piTelex instructions
    Added notes on locale configuration and updated instructions for piTelex setup.
2025-11-02 Fix mode value in RPiTTY configuration
2025-11-02 Update README with command formatting and caution note
    Corrected command formatting in README and added caution note about telex.json error.
2025-11-09 Update README with diode options
    Added additional diode options to the component list.
2025-11-18 Add README for Raspberry Pi image setup and usage
    Added detailed instructions for using the Raspberry Pi image with piTelex and i-Telex, including setup, configuration, and feedback information.
2025-11-18 Fix formatting and clarify image writing instructions
    Correct formatting and clarify instructions for writing the image to the µSD card.
2025-11-18 Add version details to README-V2.md
    Added version information for the Raspberry Pi image.
2025-11-18 Fix download link for piTelex image
    Updated download link for the image in README.
2025-11-18 Revise telex connection instructions in README
    Updated the README to clarify telex connection details and improved formatting.
2025-11-18 Enhance README with formatting and links
    Updated README-V2.md for clarity and added links.
2025-11-21 Version2
2025-11-23 Update README with SSH authentication patch info
    Added note about SSH/password authentication patch.
2025-11-23 Revise README for SSH auth patch and download link
    Updated README with patch information for SSH/password authentication and corrected download link.
2025-11-23 Update instructions for writing image to µSD card
2025-11-23 Enhance SSH workaround instructions with images
    Added images to the SSH workaround instructions in README-V2.
2025-11-23 Enhance README with additional images for SSH setup
    Added images to the SSH configuration workaround section and included a new image for the sshd_config file.
2025-11-23 Update README with improved SSH/password auth note
2025-11-23 Revise README-V2.md for clarity and formatting
    Updated formatting and corrected text in README-V2.md.
2025-11-23 Aktualisieren von README-V2.md
2025-11-24 Fehlerhafte Version 1 entfernt
2025-11-24 Revise README with SSH and piTelex instructions
    Updated instructions for modifying sshd_config and handling piTelex service.
2025-11-24 Fix typo in participant ID in README-V2.md
2025-11-24 Revise piTelex service notes in README-V2
    Updated notes regarding piTelex service restart and usage instructions.
2025-11-25 Revise README for Raspberry Pi image setup
    Updated README.md to include details about Raspberry Pi image for TW39 and V.10 hardware, installation instructions, and configuration tips.
2025-12-16 Anpassung an imager >2.0.2
2025-12-16 Revise README for RPi setup instructions
    Updated instructions for using the rpi-imager and accessing the RPi. Clarified network access and configuration steps.
2025-12-17 Refactor README.md for better organization
    Updated the README.md to improve structure and clarity by adding version headings for hardware and software components.
2025-12-17 TW39-V3 hinzugefügt
2025-12-17 Update README for TW39 power supply version
2025-12-17 Revise README for version differences and components
    Updated the README to clarify differences between versions and added a component list.
2025-12-19 Add I2C pin information to README.md
2025-12-19 Revise Version 3 details in README
    Updated the description for Version 3 to highlight GPIO changes and I2C accessibility.
2025-12-31 Revise Version 2 recommendation in README
    Updated README to recommend Version 3 for new builds due to I2C bus compatibility.
2026-01-02 Revise README with setup instructions and download links
    Updated instructions for initial setup and provided links to new and old image downloads.
2026-01-02 Revise update section with new release date
    Updated the update section with the new image release details.
2026-01-02 Fix formatting in README.md
2026-01-02 Revise README instructions for image setup and config
    Updated instructions for writing the image to the µSD card and clarified configuration steps.
2026-01-02 Modify version details in README.md
    Updated version information in README.
2026-01-02 Clarify piTelex release information in README
    Updated README to clarify piTelex release version.
2026-01-02 Add update section to README for Raspberry Pi image
    Added update information for the Raspberry Pi image.
2026-01-03 Revise README for new RPi image and configurations
    Updated README with new image details and adjustments for piTelex hardware.
2026-01-07 Add upgrade guide for old image installations
    Added upgrade instructions for installations using the old image.
2026-01-07 Update README with piTelex restoration instructions
    Added instructions for restoring the old piTelex version.
2026-01-07 Fix formatting in README for piTelex update instructions
2026-01-28 V10-3.3 (Anpassung bei optionaler TXD-LED)
2026-02-02 Add comments to configuration parameters in README
2026-02-02 Add description for D1 component in README.md
2026-02-02 Add example setup link to README
2026-02-02 Add images to Beispiel.md
2026-02-02 Revise README for Raspberry Pi configuration details
    Updated instructions for configuring the Raspberry Pi, including notes on keyboard layout and partition size.
2026-02-03 Aktualisieren von Beispiel.md
2026-02-09 HOWTO Museumstaugliche Stromversorgung
2026-02-09 Fix formatting issues in Museumstaugliche Stromversorgung doc
2026-02-09 Emphasize importance of stable 5V supply for RPi
2026-02-09 Correct efficiency notation in power calculations
2026-02-09 Fix formatting and improve clarity in power supply section
2026-02-09 Correct power calculation for DC-DC converter
2026-02-09 Improve formatting in Stromversorgung.md
    Updated formatting for better readability by adding line breaks in the instructions for using wired power switches.
2026-02-09 Clarify Tasmota-compatible sockets as WLAN devices
    Updated the description of Tasmota-compatible sockets to specify WLAN.
2026-02-11 Simplify sender circuit description in README
    Removed redundant explanation about the sender circuit's current source configuration.
2026-02-11 Simplify sender circuit description in README
    Removed unnecessary details about the sender circuit while retaining essential information.
2026-02-11 Update README to remove short-circuit safety details
    Removed mention of short-circuit safety in the sender circuit description.
2026-02-12 Revise configuration instructions in README.md
2026-02-12 Add localization and keyboard layout instructions
2026-03-04 Update line current adjustment instructions in README
    Clarified the adjustment process for the line current setting.
2026-03-19 Aufbaubeispiel für museumstaugliches piTelex-FSG aufgenommen
2026-03-19 Fix link for Aufbau example in README.md
2026-03-19 Update link for piTelex Release 2025-12a
2026-03-19 Update README with more photos and a video link
    Added additional images and a video link to the README.
2026-03-19 Enhance README with new components and curl command fix
    Updated README.md with additional components and modified curl command outputs.
2026-03-19 Add setup example for piTelex-FSG
    Added a section with a setup example for piTelex-FSG.
2026-03-19 Revise README with assembly notes and modifications
    Updated notes on the assembly and modifications of components, including the snap fastening and the repurposing of the earth button.
2026-03-19 Fix GPIO pin reference and enhance comments in README
    Updated GPIO pin reference for relay control and added comments for clarity.
2026-03-19 Aufräumen
2026-03-19 Update README to remove TW39 version details
    Removed details about TW39 hardware versions 1 and 2, and added a note to version 3 regarding GPIO changes.
2026-03-24 kombiplatine
2026-03-30 add TWB-Anpassung
2026-03-30 Update README.md for image alignment and details
2026-04-02 Add disclaimer to README
    Added a disclaimer regarding liability and safety responsibilities.
2026-04-02 Bild korrigiert
2026-04-14 Fix formatting in README.md for J9 connections
2026-04-22 Update README with configuration instructions
